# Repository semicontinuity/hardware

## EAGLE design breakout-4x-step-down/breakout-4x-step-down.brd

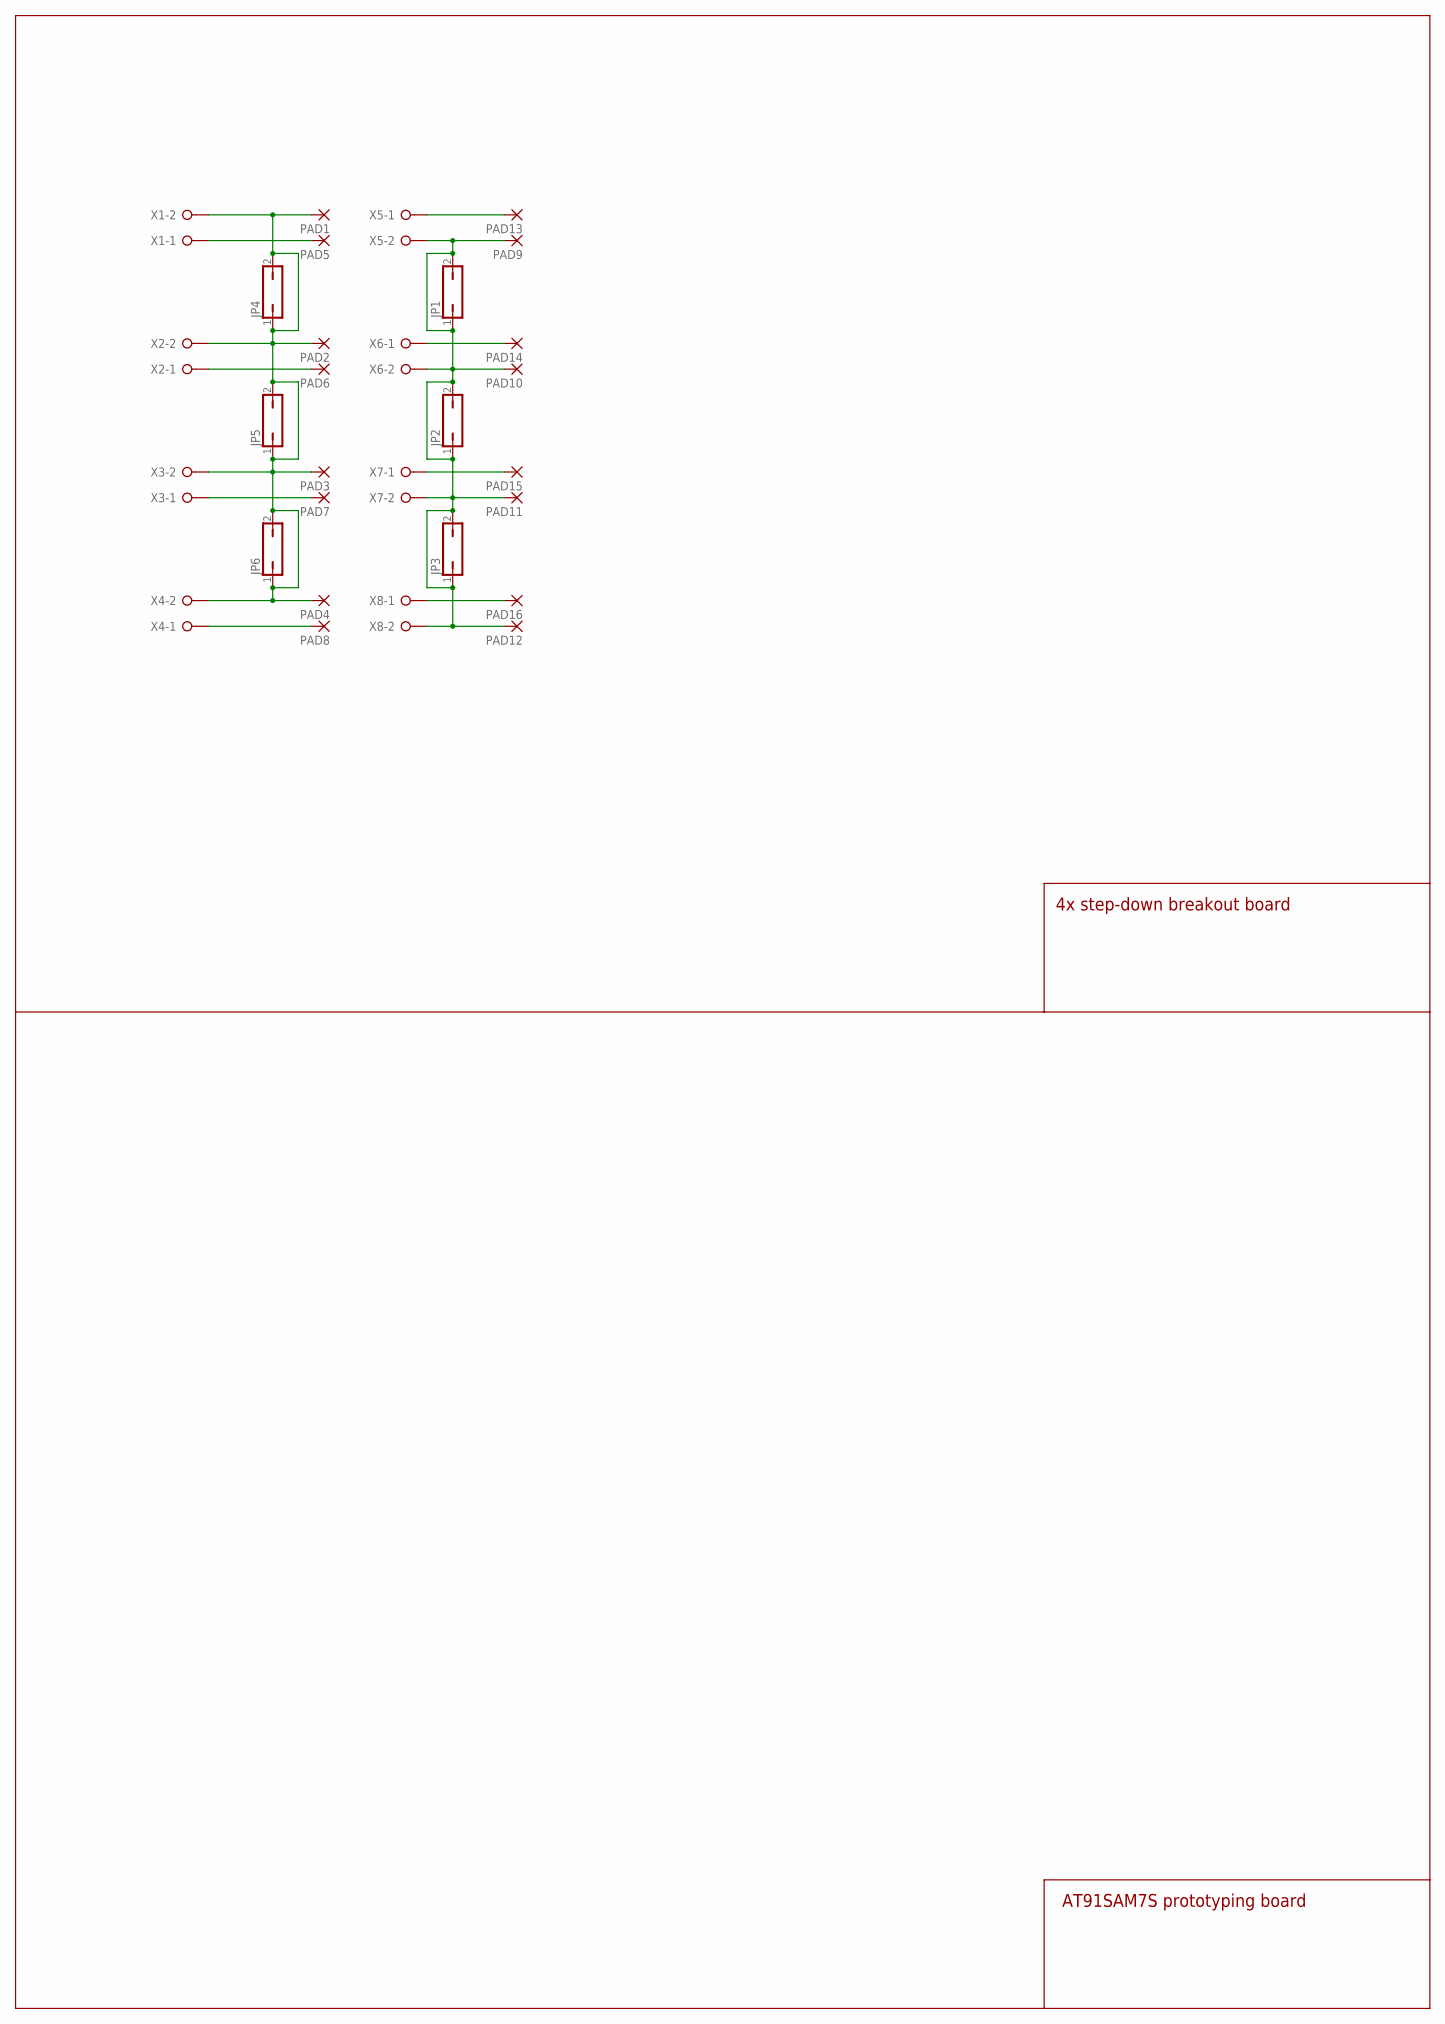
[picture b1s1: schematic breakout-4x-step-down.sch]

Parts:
JP1, JP2, JP3, JP4, JP5, JP6: JP1Q; JP1
PAD1, PAD2, PAD3, PAD4, PAD5, PAD6, PAD7, PAD8, PAD9, PAD10, PAD11, PAD12, PAD13, PAD14, PAD15, PAD16: 1,6/0,8
X1, X2, X3, X4, X5, X6, X7, X8: W237-02P; W237-132

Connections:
unnamed: JP4.1, JP4.2, JP5.1, JP5.2, JP6.1, JP6.2, PAD1.1, PAD2.1, PAD3.1, PAD4.1, X1.2, X2.2, X3.2, X4.2
unnamed: PAD5.1, X1.1
unnamed: JP1.1, JP1.2, JP2.1, JP2.2, JP3.1, JP3.2, PAD9.1, PAD10.1, PAD11.1, PAD12.1, X5.2, X6.2, X7.2, X8.2
unnamed: PAD6.1, X2.1
unnamed: PAD7.1, X3.1
unnamed: PAD8.1, X4.1
unnamed: PAD16.1, X8.1
unnamed: PAD15.1, X7.1
unnamed: PAD14.1, X6.1
unnamed: PAD13.1, X5.1

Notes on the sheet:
4x step-down breakout board
AT91SAM7S prototyping board

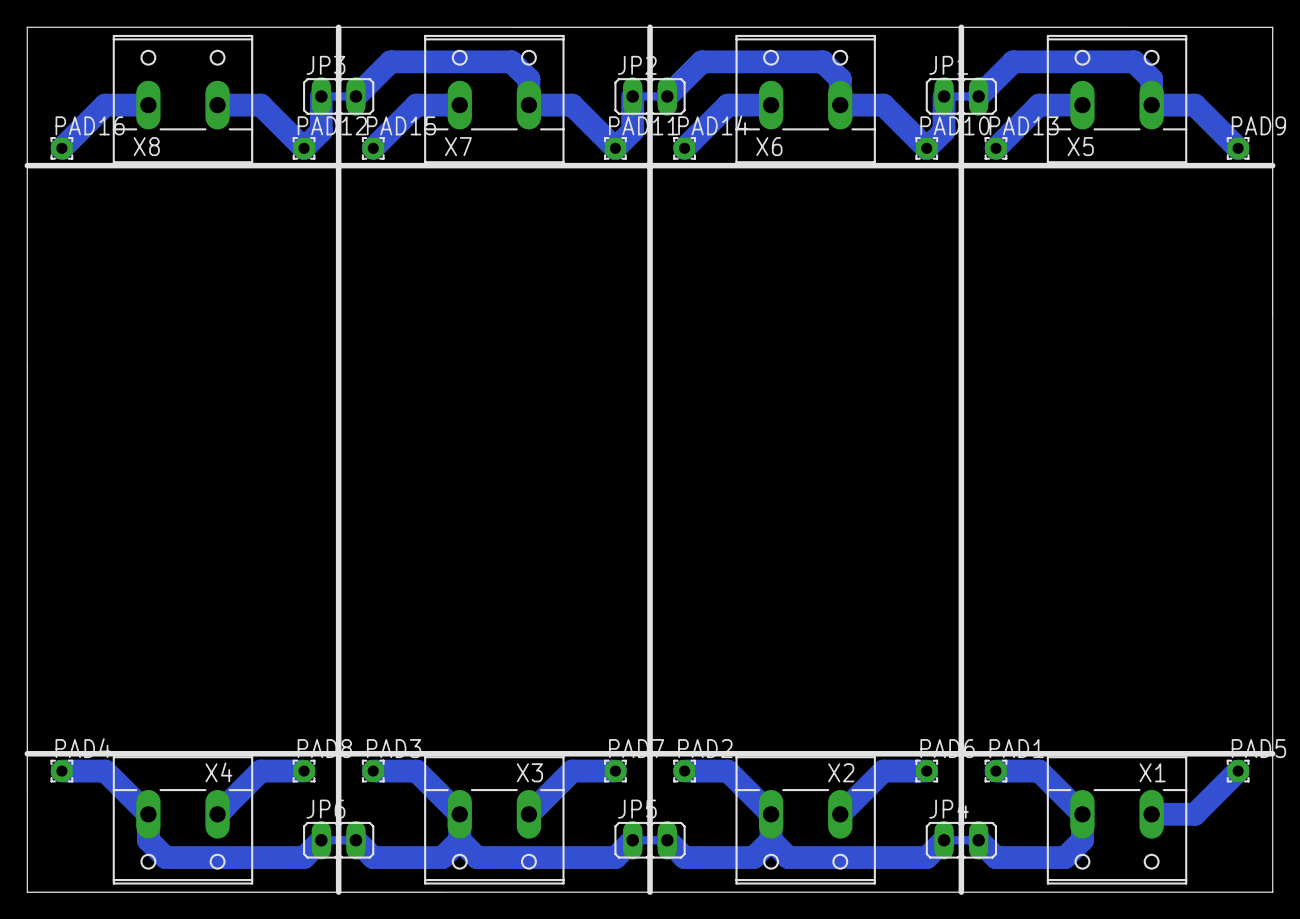
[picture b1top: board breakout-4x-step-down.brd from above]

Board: 2 copper layers, 91.4 x 63.5 mm, 30 parts (0 on the bottom side), 10 nets.
